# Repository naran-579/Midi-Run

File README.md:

# Midi Run
A custom MIDI keypad with switches, sliders, rotary encoders, neopixels and capacitive buttons

# What makes mine unique (hardware-wise)
- Tried some copper art
- Simpler keypad footprint
- Much more convoluted pcb layout

I would've added more but I ran out of IO  

# What makes mine unique (software-wise)
- Volume is now connected to the press
- A sort of glissando mode
- USB identity
- Actual circuitpy compatibility

# BOM
| Item                                        | Qty | Supplier  | Cost/item | Total Cost | link                                                                                                                                 |
|---------------------------------------------|-----|-----------|-----------|------------|--------------------------------------------------------------------------------------------------------------------------------------|
| Esp32                                       | 1   | Waveshare | $6.49     | $6.49      | https://www.waveshare.com/esp32-s3-zero.htm?sku=25517                                                                                |
| Neopixels                                   | 1   | Adafruit  | $2.95     | $2.95      | https://www.adafruit.com/product/4960                                                                                                |
| PCB                                         | 1   | JLCPCB    | $9.30     | $9.30      | https://cart.jlcpcb.com/quote?stencilLayer=2&stencilWidth=100&stencilLength=100&stencilCounts=5&plateType=1&spm=Jlcpcb.Homepage.1010 |
| Kalih choc low profile switches (10pc pack) | 1   | KALIH     | $10.99    | $10.99     | https://www.amazon.com/dp/B0B461YJ2D?lv=shuf&channelId=520&plpRedirect=mhFallback                                                    |
| rotary encoder                              | 1   | Digikey   | $1.97     | $1.97      | https://www.digikey.com/en/products/detail/bourns-inc/PEC11R-4025F-N0024/4499638                                                     |
| Slide potentiometer                         | 2   | Digikey   | $1.58     | $3.16      | https://www.digikey.com/en/products/detail/bourns-inc/PTA1543-2015CPB103/3781165                                                     |
| Estimated total shipping                    | 1   |           |           | $0.00      |                                                                                                                                      |

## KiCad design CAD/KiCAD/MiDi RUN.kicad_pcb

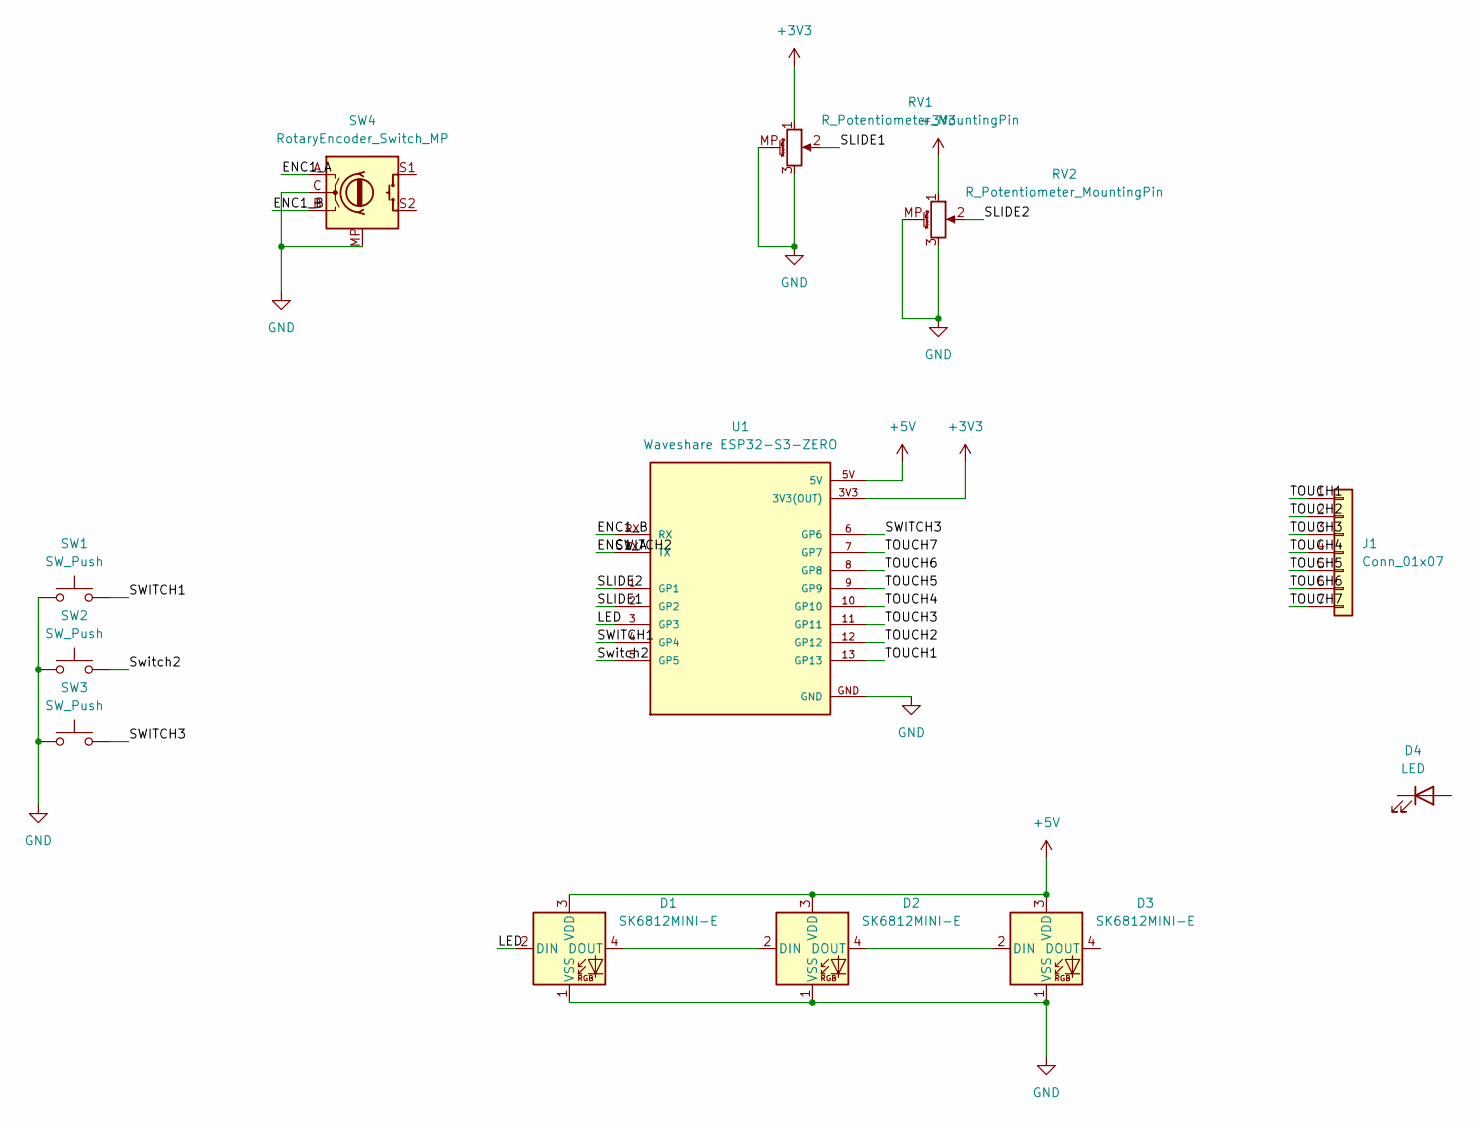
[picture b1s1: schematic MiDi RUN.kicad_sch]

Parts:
D1, D2, D3: SK6812MINI-E; LED_SK6812MINI-E_3.2x2.8mm_P1.5mm_ReverseMount
D4: LED; Untitled_1
J1: Conn_01x07; Untitled
RV1, RV2: R_Potentiometer_MountingPin; Potentiometer_Bourns_PTA1543_Single_Slide
SW1, SW2, SW3: SW_Push; Kailh Choc Low-Profile Switches
SW4: RotaryEncoder_Switch_MP; RotaryEncoder_Alps_EC11E-Switch_Vertical_H20mm
U1: Waveshare ESP32-S3-ZERO; Waveshare ESP32-S3-Zero; PARTREV NA

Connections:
+3V3: RV1.1, RV2.1, U1.3V3 (3V3(OUT))
+5V: D1.3 (VDD), D2.3 (VDD), D3.3 (VDD), U1.5V
/ENC1_A: SW4.A, U1.TX
/ENC1_B: SW4.B, U1.RX
/LED: D1.2 (DIN), U1.3 (GP3)
/SLIDE1: RV1.2, U1.2 (GP2)
/SLIDE2: RV2.2, U1.1 (GP1)
/SWITCH1: SW1.2, U1.4 (GP4)
/SWITCH3: SW3.2, U1.6 (GP6)
/Switch2: SW2.2, U1.5 (GP5)
/TOUCH1: J1.1, U1.13 (GP13)
/TOUCH2: J1.2, U1.12 (GP12)
/TOUCH3: J1.3, U1.11 (GP11)
/TOUCH4: J1.4, U1.10 (GP10)
/TOUCH5: J1.5, U1.9 (GP9)
/TOUCH6: J1.6, U1.8 (GP8)
/TOUCH7: J1.7, U1.7 (GP7)
GND: D1.1 (VSS), D2.1 (VSS), D3.1 (VSS), RV1.3, RV1.MP (MountPin), RV2.3, RV2.MP (MountPin), SW1.1, SW2.1, SW3.1, SW4.C, SW4.MP, U1.GND
unnamed: D1.4 (DOUT), D2.2 (DIN)
unnamed: D2.4 (DOUT), D3.2 (DIN)

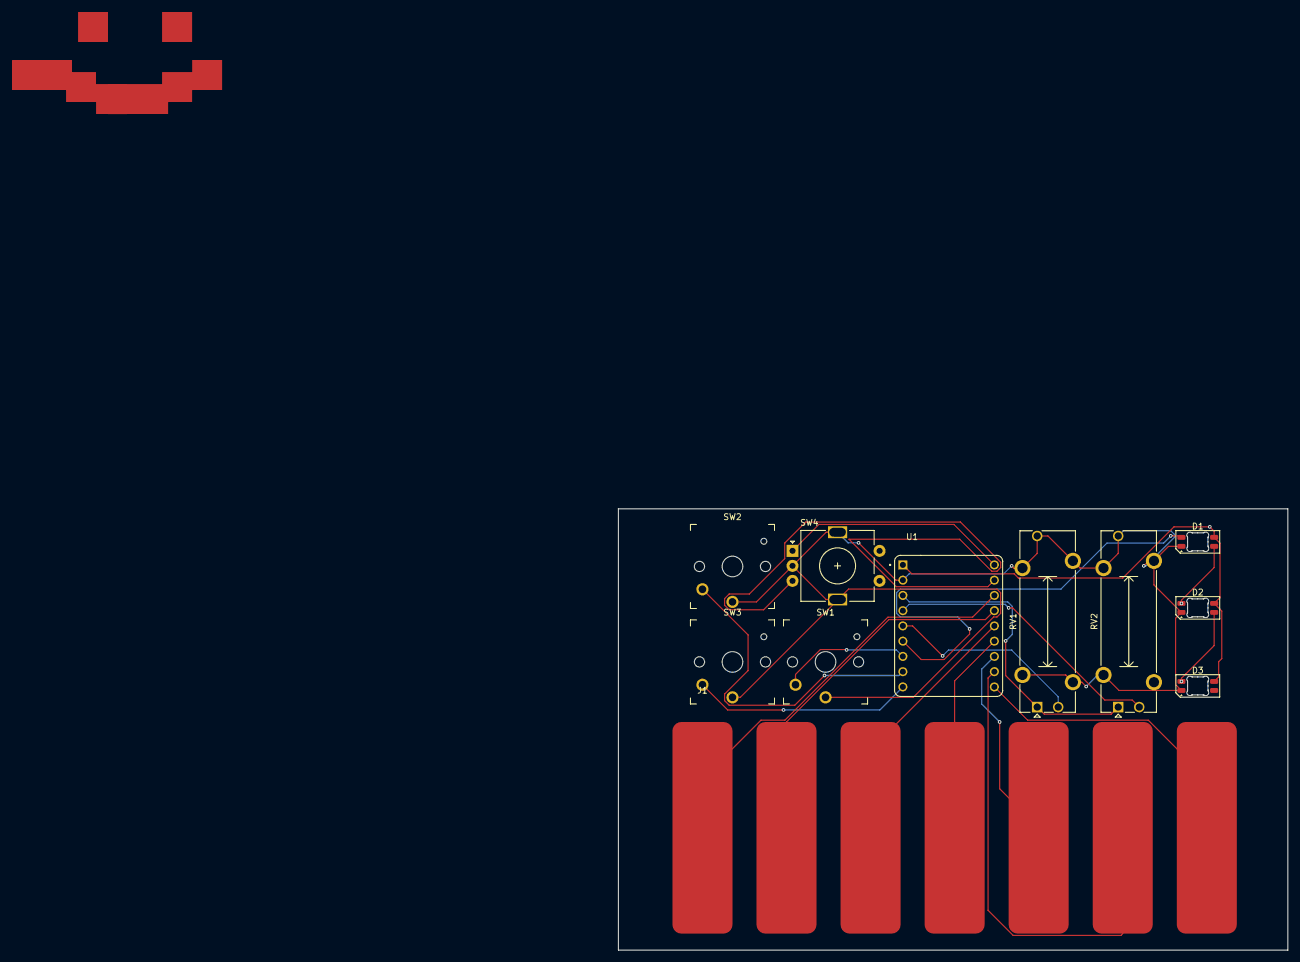
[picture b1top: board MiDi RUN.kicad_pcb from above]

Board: 2 copper layers, 111.5 x 73.5 mm, 12 parts (0 on the bottom side), 20 nets.
